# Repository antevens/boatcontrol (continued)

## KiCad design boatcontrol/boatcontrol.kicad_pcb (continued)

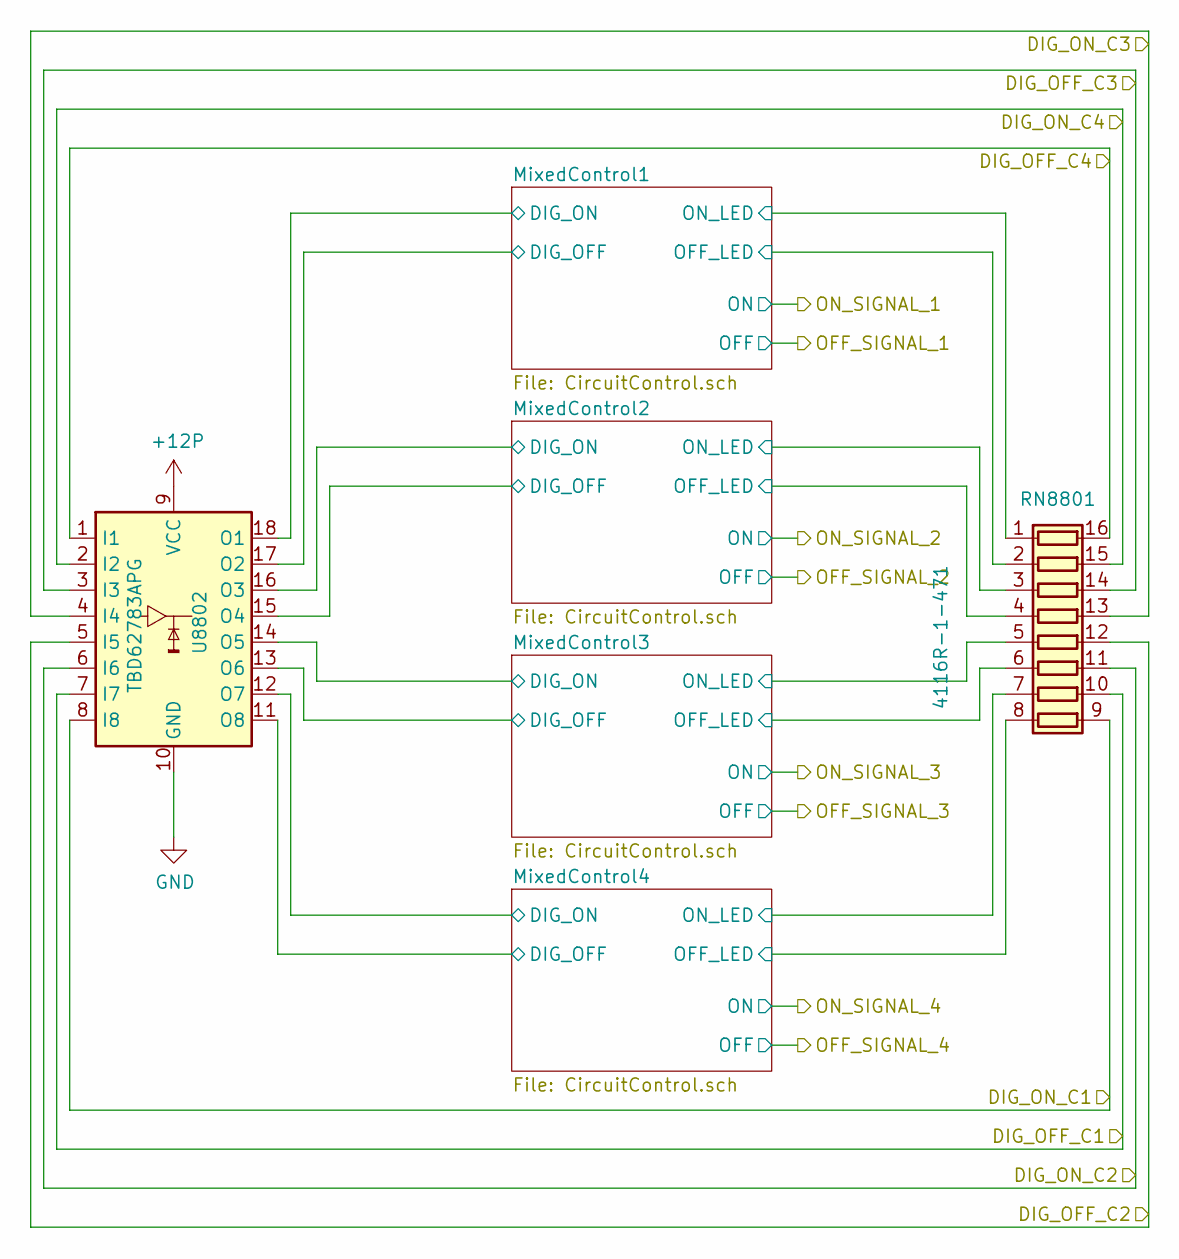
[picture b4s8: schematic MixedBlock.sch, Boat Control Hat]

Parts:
RN4001: 4116R-1-471; DIP254P762X432-16P
U4001: TBD62783APG; DIP-18_W7.62mm

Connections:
+12P: U4001.9 (VCC); also elsewhere on the board
/Add-On Relay Board 1/ADDON_C1_OFF: RN4001.10 (R7.2), U4001.7 (I7); also elsewhere on the board
/Add-On Relay Board 1/ADDON_C1_ON: RN4001.9 (R8.2), U4001.8 (I8); also elsewhere on the board
/Add-On Relay Board 1/ADDON_C2_OFF: RN4001.12 (R5.2), U4001.5 (I5); also elsewhere on the board
/Add-On Relay Board 1/ADDON_C2_ON: RN4001.11 (R6.2), U4001.6 (I6); also elsewhere on the board
/Add-On Relay Board 1/ADDON_C3_OFF: RN4001.14 (R3.2), U4001.3 (I3); also elsewhere on the board
/Add-On Relay Board 1/ADDON_C3_ON: RN4001.13 (R4.2), U4001.4 (I4); also elsewhere on the board
/Add-On Relay Board 1/ADDON_C4_OFF: RN4001.16 (R1.2), U4001.1 (I1); also elsewhere on the board
/Add-On Relay Board 1/ADDON_C4_ON: RN4001.15 (R2.2), U4001.2 (I2); also elsewhere on the board
/Add-On Relay Board 1/MixedBlock1/MixedControl1/DIG_OFF: U4001.17 (O2); also elsewhere on the board
/Add-On Relay Board 1/MixedBlock1/MixedControl1/DIG_ON: U4001.18 (O1); also elsewhere on the board
/Add-On Relay Board 1/MixedBlock1/MixedControl1/OFF_LED: RN4001.2 (R2.1); also elsewhere on the board
/Add-On Relay Board 1/MixedBlock1/MixedControl1/ON_LED: RN4001.1 (R1.1); also elsewhere on the board
/Add-On Relay Board 1/MixedBlock1/MixedControl2/DIG_OFF: U4001.15 (O4); also elsewhere on the board
/Add-On Relay Board 1/MixedBlock1/MixedControl2/DIG_ON: U4001.16 (O3); also elsewhere on the board
/Add-On Relay Board 1/MixedBlock1/MixedControl2/OFF_LED: RN4001.4 (R4.1); also elsewhere on the board
/Add-On Relay Board 1/MixedBlock1/MixedControl2/ON_LED: RN4001.3 (R3.1); also elsewhere on the board
/Add-On Relay Board 1/MixedBlock1/MixedControl3/DIG_OFF: U4001.13 (O6); also elsewhere on the board
/Add-On Relay Board 1/MixedBlock1/MixedControl3/DIG_ON: U4001.14 (O5); also elsewhere on the board
/Add-On Relay Board 1/MixedBlock1/MixedControl3/OFF_LED: RN4001.6 (R6.1); also elsewhere on the board
/Add-On Relay Board 1/MixedBlock1/MixedControl3/ON_LED: RN4001.5 (R5.1); also elsewhere on the board
/Add-On Relay Board 1/MixedBlock1/MixedControl4/DIG_OFF: U4001.11 (O8); also elsewhere on the board
/Add-On Relay Board 1/MixedBlock1/MixedControl4/DIG_ON: U4001.12 (O7); also elsewhere on the board
/Add-On Relay Board 1/MixedBlock1/MixedControl4/OFF_LED: RN4001.8 (R8.1); also elsewhere on the board
/Add-On Relay Board 1/MixedBlock1/MixedControl4/ON_LED: RN4001.7 (R7.1); also elsewhere on the board
GND: U4001.10 (GND); also elsewhere on the board

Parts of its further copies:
RN4501, RN8801, RN9301: 4116R-1-471; DIP254P762X432-16P
U4501, U8802, U9301: TBD62783APG; DIP-18_W7.62mm

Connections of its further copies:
+12P: U4501.9 (VCC), U8802.9 (VCC), U9301.9 (VCC); also elsewhere on the board
/Add-On Relay Board 1/ADDON_C5_OFF: RN4501.10 (R7.2), U4501.7 (I7); also elsewhere on the board
/Add-On Relay Board 1/ADDON_C5_ON: RN4501.9 (R8.2), U4501.8 (I8); also elsewhere on the board
/Add-On Relay Board 1/ADDON_C6_OFF: RN4501.12 (R5.2), U4501.5 (I5); also elsewhere on the board
/Add-On Relay Board 1/ADDON_C6_ON: RN4501.11 (R6.2), U4501.6 (I6); also elsewhere on the board
/Add-On Relay Board 1/ADDON_C7_OFF: RN4501.14 (R3.2), U4501.3 (I3); also elsewhere on the board
/Add-On Relay Board 1/ADDON_C7_ON: RN4501.13 (R4.2), U4501.4 (I4); also elsewhere on the board
/Add-On Relay Board 1/ADDON_C8_OFF: RN4501.16 (R1.2), U4501.1 (I1); also elsewhere on the board
/Add-On Relay Board 1/ADDON_C8_ON: RN4501.15 (R2.2), U4501.2 (I2); also elsewhere on the board
/Add-On Relay Board 1/MixedBlock2/MixedControl1/DIG_OFF: U4501.17 (O2); also elsewhere on the board
/Add-On Relay Board 1/MixedBlock2/MixedControl1/DIG_ON: U4501.18 (O1); also elsewhere on the board
/Add-On Relay Board 1/MixedBlock2/MixedControl1/OFF_LED: RN4501.2 (R2.1); also elsewhere on the board
/Add-On Relay Board 1/MixedBlock2/MixedControl1/ON_LED: RN4501.1 (R1.1); also elsewhere on the board
/Add-On Relay Board 1/MixedBlock2/MixedControl2/DIG_OFF: U4501.15 (O4); also elsewhere on the board
/Add-On Relay Board 1/MixedBlock2/MixedControl2/DIG_ON: U4501.16 (O3); also elsewhere on the board
/Add-On Relay Board 1/MixedBlock2/MixedControl2/OFF_LED: RN4501.4 (R4.1); also elsewhere on the board
/Add-On Relay Board 1/MixedBlock2/MixedControl2/ON_LED: RN4501.3 (R3.1); also elsewhere on the board
/Add-On Relay Board 1/MixedBlock2/MixedControl3/DIG_OFF: U4501.13 (O6); also elsewhere on the board
/Add-On Relay Board 1/MixedBlock2/MixedControl3/DIG_ON: U4501.14 (O5); also elsewhere on the board
/Add-On Relay Board 1/MixedBlock2/MixedControl3/OFF_LED: RN4501.6 (R6.1); also elsewhere on the board
/Add-On Relay Board 1/MixedBlock2/MixedControl3/ON_LED: RN4501.5 (R5.1); also elsewhere on the board
/Add-On Relay Board 1/MixedBlock2/MixedControl4/DIG_OFF: U4501.11 (O8); also elsewhere on the board
/Add-On Relay Board 1/MixedBlock2/MixedControl4/DIG_ON: U4501.12 (O7); also elsewhere on the board
/Add-On Relay Board 1/MixedBlock2/MixedControl4/OFF_LED: RN4501.8 (R8.1); also elsewhere on the board
/Add-On Relay Board 1/MixedBlock2/MixedControl4/ON_LED: RN4501.7 (R7.1); also elsewhere on the board
/Add-On Relay Board 2/ADDON_C1_OFF: RN8801.10 (R7.2), U8802.7 (I7); also elsewhere on the board
/Add-On Relay Board 2/ADDON_C1_ON: RN8801.9 (R8.2), U8802.8 (I8); also elsewhere on the board
/Add-On Relay Board 2/ADDON_C2_OFF: RN8801.12 (R5.2), U8802.5 (I5); also elsewhere on the board
/Add-On Relay Board 2/ADDON_C2_ON: RN8801.11 (R6.2), U8802.6 (I6); also elsewhere on the board
/Add-On Relay Board 2/ADDON_C3_OFF: RN8801.14 (R3.2), U8802.3 (I3); also elsewhere on the board
/Add-On Relay Board 2/ADDON_C3_ON: RN8801.13 (R4.2), U8802.4 (I4); also elsewhere on the board
/Add-On Relay Board 2/ADDON_C4_OFF: RN8801.16 (R1.2), U8802.1 (I1); also elsewhere on the board
/Add-On Relay Board 2/ADDON_C4_ON: RN8801.15 (R2.2), U8802.2 (I2); also elsewhere on the board
/Add-On Relay Board 2/ADDON_C5_OFF: RN9301.10 (R7.2), U9301.7 (I7); also elsewhere on the board
/Add-On Relay Board 2/ADDON_C5_ON: RN9301.9 (R8.2), U9301.8 (I8); also elsewhere on the board
/Add-On Relay Board 2/ADDON_C6_OFF: RN9301.12 (R5.2), U9301.5 (I5); also elsewhere on the board
/Add-On Relay Board 2/ADDON_C6_ON: RN9301.11 (R6.2), U9301.6 (I6); also elsewhere on the board
/Add-On Relay Board 2/ADDON_C7_OFF: RN9301.14 (R3.2), U9301.3 (I3); also elsewhere on the board
/Add-On Relay Board 2/ADDON_C7_ON: RN9301.13 (R4.2), U9301.4 (I4); also elsewhere on the board
/Add-On Relay Board 2/ADDON_C8_OFF: RN9301.16 (R1.2), U9301.1 (I1); also elsewhere on the board
/Add-On Relay Board 2/ADDON_C8_ON: RN9301.15 (R2.2), U9301.2 (I2); also elsewhere on the board
/Add-On Relay Board 2/MixedBlock1/MixedControl1/DIG_OFF: U8802.17 (O2); also elsewhere on the board
/Add-On Relay Board 2/MixedBlock1/MixedControl1/DIG_ON: U8802.18 (O1); also elsewhere on the board
/Add-On Relay Board 2/MixedBlock1/MixedControl1/OFF_LED: RN8801.2 (R2.1); also elsewhere on the board
/Add-On Relay Board 2/MixedBlock1/MixedControl1/ON_LED: RN8801.1 (R1.1); also elsewhere on the board
/Add-On Relay Board 2/MixedBlock1/MixedControl2/DIG_OFF: U8802.15 (O4); also elsewhere on the board
/Add-On Relay Board 2/MixedBlock1/MixedControl2/DIG_ON: U8802.16 (O3); also elsewhere on the board
/Add-On Relay Board 2/MixedBlock1/MixedControl2/OFF_LED: RN8801.4 (R4.1); also elsewhere on the board
/Add-On Relay Board 2/MixedBlock1/MixedControl2/ON_LED: RN8801.3 (R3.1); also elsewhere on the board
/Add-On Relay Board 2/MixedBlock1/MixedControl3/DIG_OFF: U8802.13 (O6); also elsewhere on the board
/Add-On Relay Board 2/MixedBlock1/MixedControl3/DIG_ON: U8802.14 (O5); also elsewhere on the board
/Add-On Relay Board 2/MixedBlock1/MixedControl3/OFF_LED: RN8801.6 (R6.1); also elsewhere on the board
/Add-On Relay Board 2/MixedBlock1/MixedControl3/ON_LED: RN8801.5 (R5.1); also elsewhere on the board
/Add-On Relay Board 2/MixedBlock1/MixedControl4/DIG_OFF: U8802.11 (O8); also elsewhere on the board
/Add-On Relay Board 2/MixedBlock1/MixedControl4/DIG_ON: U8802.12 (O7); also elsewhere on the board
/Add-On Relay Board 2/MixedBlock1/MixedControl4/OFF_LED: RN8801.8 (R8.1); also elsewhere on the board
/Add-On Relay Board 2/MixedBlock1/MixedControl4/ON_LED: RN8801.7 (R7.1); also elsewhere on the board
/Add-On Relay Board 2/MixedBlock2/MixedControl1/DIG_OFF: U9301.17 (O2); also elsewhere on the board
/Add-On Relay Board 2/MixedBlock2/MixedControl1/DIG_ON: U9301.18 (O1); also elsewhere on the board
/Add-On Relay Board 2/MixedBlock2/MixedControl1/OFF_LED: RN9301.2 (R2.1); also elsewhere on the board
/Add-On Relay Board 2/MixedBlock2/MixedControl1/ON_LED: RN9301.1 (R1.1); also elsewhere on the board
/Add-On Relay Board 2/MixedBlock2/MixedControl2/DIG_OFF: U9301.15 (O4); also elsewhere on the board
/Add-On Relay Board 2/MixedBlock2/MixedControl2/DIG_ON: U9301.16 (O3); also elsewhere on the board
/Add-On Relay Board 2/MixedBlock2/MixedControl2/OFF_LED: RN9301.4 (R4.1); also elsewhere on the board
/Add-On Relay Board 2/MixedBlock2/MixedControl2/ON_LED: RN9301.3 (R3.1); also elsewhere on the board
/Add-On Relay Board 2/MixedBlock2/MixedControl3/DIG_OFF: U9301.13 (O6); also elsewhere on the board
/Add-On Relay Board 2/MixedBlock2/MixedControl3/DIG_ON: U9301.14 (O5); also elsewhere on the board
/Add-On Relay Board 2/MixedBlock2/MixedControl3/OFF_LED: RN9301.6 (R6.1); also elsewhere on the board
/Add-On Relay Board 2/MixedBlock2/MixedControl3/ON_LED: RN9301.5 (R5.1); also elsewhere on the board
/Add-On Relay Board 2/MixedBlock2/MixedControl4/DIG_OFF: U9301.11 (O8); also elsewhere on the board
/Add-On Relay Board 2/MixedBlock2/MixedControl4/DIG_ON: U9301.12 (O7); also elsewhere on the board
/Add-On Relay Board 2/MixedBlock2/MixedControl4/OFF_LED: RN9301.8 (R8.1); also elsewhere on the board
/Add-On Relay Board 2/MixedBlock2/MixedControl4/ON_LED: RN9301.7 (R7.1); also elsewhere on the board
GND: U4501.10 (GND), U8802.10 (GND), U9301.10 (GND); also elsewhere on the board

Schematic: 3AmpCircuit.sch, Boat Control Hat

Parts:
CB1101: T9-818 3; Schurter_Circuit_Breaker
D1101: 20mA R/G CA; LED_D5.0mm-3
K1101: G5RL-K1A-E-DC12; RELAY_G5RL-K1A-E-DC12
SW1101, SW1102: ESB30; SW_PUSH_ESB30_DPDT

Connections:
+12C: K1101.3 (NC), K1101.6 (NC); also elsewhere on the board
+12P: D1101.2 (K), K1101.9 (C9); also elsewhere on the board
/12V DC Common Bank/12V DC Block 1/3AC1/DISABLED_INDICATOR: SW1101.3 (C), SW1102.3 (C)
/12V DC Common Bank/12V DC Block 1/3AC1/OFF: SW1101.4 (A); also elsewhere on the board
/12V DC Common Bank/12V DC Block 1/3AC1/OFF_COIL: K1101.8 (C8), SW1102.2 (B); also elsewhere on the board
/12V DC Common Bank/12V DC Block 1/3AC1/OFF_LED: D1101.3 (A2); also elsewhere on the board
/12V DC Common Bank/12V DC Block 1/3AC1/OFF_TO_ON: SW1101.5 (B), SW1102.1 (A)
/12V DC Common Bank/12V DC Block 1/3AC1/ON: SW1102.4 (A); also elsewhere on the board
/12V DC Common Bank/12V DC Block 1/3AC1/ON_COIL: K1101.1 (C1), SW1101.2 (B); also elsewhere on the board
/12V DC Common Bank/12V DC Block 1/3AC1/ON_LED: D1101.1 (A1); also elsewhere on the board
/12V DC Common Bank/12V DC Block 1/3AC1/ON_TO_OFF: SW1101.1 (A), SW1102.5 (B)
/12V DC Common Bank/12V DC Block 1/3AC1/TO_FUSE: CB1101.P1, K1101.4 (NO), K1101.5 (NO)
/12V DC Common Bank/12V DC Block 1/OUT_C1: CB1101.P2; also elsewhere on the board
GND: SW1101.6 (C), SW1102.6 (C); also elsewhere on the board

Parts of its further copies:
CB801, CB901, CB1001, CB1701, CB1801, CB1901, CB2001, CB2601, CB2701, CB2801, CB2901, CB3501, CB3601, CB3701, CB3801: T9-818 3; Schurter_Circuit_Breaker
D801, D901, D1001, D1701, D1801, D1901, D2001, D2601, D2701, D2801, D2901, D3501, D3601, D3701, D3801: 20mA R/G CA; LED_D5.0mm-3
K801, K901, K1001, K1701, K1801, K1901, K2001, K2601, K2701, K2801, K2901, K3501, K3601, K3701, K3801: G5RL-K1A-E-DC12; RELAY_G5RL-K1A-E-DC12
SW801, SW802, SW901, SW902, SW1001, SW1002, SW1701, SW1702, SW1801, SW1802, SW1901, SW1902, SW2001, SW2002, SW2601, SW2602, SW2701, SW2702, SW2801, SW2802, SW2901, SW2902, SW3501, SW3502, SW3601, SW3602, SW3701, SW3702, SW3801, SW3802: ESB30; SW_PUSH_ESB30_DPDT

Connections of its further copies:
+12C: K801.3 (NC), K801.6 (NC), K901.3 (NC), K901.6 (NC), K1001.3 (NC), K1001.6 (NC), K1701.3 (NC), K1701.6 (NC), K1801.3 (NC), K1801.6 (NC), K1901.3 (NC), K1901.6 (NC), K2001.3 (NC), K2001.6 (NC), K2601.3 (NC), K2601.6 (NC), K2701.3 (NC), K2701.6 (NC), K2801.3 (NC), K2801.6 (NC), K2901.3 (NC), K2901.6 (NC), K3501.3 (NC), K3501.6 (NC), K3601.3 (NC), K3601.6 (NC), K3701.3 (NC), K3701.6 (NC), K3801.3 (NC), K3801.6 (NC); also elsewhere on the board
+12P: D801.2 (K), D901.2 (K), D1001.2 (K), D1701.2 (K), D1801.2 (K), D1901.2 (K), D2001.2 (K), D2601.2 (K), D2701.2 (K), D2801.2 (K), D2901.2 (K), D3501.2 (K), D3601.2 (K), D3701.2 (K), D3801.2 (K), K801.9 (C9), K901.9 (C9), K1001.9 (C9), K1701.9 (C9), K1801.9 (C9), K1901.9 (C9), K2001.9 (C9), K2601.9 (C9), K2701.9 (C9), K2801.9 (C9), K2901.9 (C9), K3501.9 (C9), K3601.9 (C9), K3701.9 (C9), K3801.9 (C9); also elsewhere on the board
/12V DC Common Bank/12V DC Block 1/3AC2/DISABLED_INDICATOR: SW1001.3 (C), SW1002.3 (C)
/12V DC Common Bank/12V DC Block 1/3AC2/OFF: SW1001.4 (A); also elsewhere on the board
/12V DC Common Bank/12V DC Block 1/3AC2/OFF_COIL: K1001.8 (C8), SW1002.2 (B); also elsewhere on the board
/12V DC Common Bank/12V DC Block 1/3AC2/OFF_LED: D1001.3 (A2); also elsewhere on the board
/12V DC Common Bank/12V DC Block 1/3AC2/OFF_TO_ON: SW1001.5 (B), SW1002.1 (A)
/12V DC Common Bank/12V DC Block 1/3AC2/ON: SW1002.4 (A); also elsewhere on the board
/12V DC Common Bank/12V DC Block 1/3AC2/ON_COIL: K1001.1 (C1), SW1001.2 (B); also elsewhere on the board
/12V DC Common Bank/12V DC Block 1/3AC2/ON_LED: D1001.1 (A1); also elsewhere on the board
/12V DC Common Bank/12V DC Block 1/3AC2/ON_TO_OFF: SW1001.1 (A), SW1002.5 (B)
/12V DC Common Bank/12V DC Block 1/3AC2/TO_FUSE: CB1001.P1, K1001.4 (NO), K1001.5 (NO)
/12V DC Common Bank/12V DC Block 1/3AC3/DISABLED_INDICATOR: SW901.3 (C), SW902.3 (C)
/12V DC Common Bank/12V DC Block 1/3AC3/OFF: SW901.4 (A); also elsewhere on the board
/12V DC Common Bank/12V DC Block 1/3AC3/OFF_COIL: K901.8 (C8), SW902.2 (B); also elsewhere on the board
/12V DC Common Bank/12V DC Block 1/3AC3/OFF_LED: D901.3 (A2); also elsewhere on the board
/12V DC Common Bank/12V DC Block 1/3AC3/OFF_TO_ON: SW901.5 (B), SW902.1 (A)
/12V DC Common Bank/12V DC Block 1/3AC3/ON: SW902.4 (A); also elsewhere on the board
/12V DC Common Bank/12V DC Block 1/3AC3/ON_COIL: K901.1 (C1), SW901.2 (B); also elsewhere on the board
/12V DC Common Bank/12V DC Block 1/3AC3/ON_LED: D901.1 (A1); also elsewhere on the board
/12V DC Common Bank/12V DC Block 1/3AC3/ON_TO_OFF: SW901.1 (A), SW902.5 (B)
/12V DC Common Bank/12V DC Block 1/3AC3/TO_FUSE: CB901.P1, K901.4 (NO), K901.5 (NO)
/12V DC Common Bank/12V DC Block 1/3AC4/DISABLED_INDICATOR: SW801.3 (C), SW802.3 (C)
/12V DC Common Bank/12V DC Block 1/3AC4/OFF: SW801.4 (A); also elsewhere on the board
/12V DC Common Bank/12V DC Block 1/3AC4/OFF_COIL: K801.8 (C8), SW802.2 (B); also elsewhere on the board
/12V DC Common Bank/12V DC Block 1/3AC4/OFF_LED: D801.3 (A2); also elsewhere on the board
/12V DC Common Bank/12V DC Block 1/3AC4/OFF_TO_ON: SW801.5 (B), SW802.1 (A)
/12V DC Common Bank/12V DC Block 1/3AC4/ON: SW802.4 (A); also elsewhere on the board
/12V DC Common Bank/12V DC Block 1/3AC4/ON_COIL: K801.1 (C1), SW801.2 (B); also elsewhere on the board
/12V DC Common Bank/12V DC Block 1/3AC4/ON_LED: D801.1 (A1); also elsewhere on the board
/12V DC Common Bank/12V DC Block 1/3AC4/ON_TO_OFF: SW801.1 (A), SW802.5 (B)
/12V DC Common Bank/12V DC Block 1/3AC4/TO_FUSE: CB801.P1, K801.4 (NO), K801.5 (NO)
/12V DC Common Bank/12V DC Block 1/OUT_C2: CB1001.P2; also elsewhere on the board
/12V DC Common Bank/12V DC Block 1/OUT_C3: CB901.P2; also elsewhere on the board
/12V DC Common Bank/12V DC Block 1/OUT_C4: CB801.P2; also elsewhere on the board
/12V DC Common Bank/12V DC Block 2/3AC1/DISABLED_INDICATOR: SW2001.3 (C), SW2002.3 (C)
/12V DC Common Bank/12V DC Block 2/3AC1/OFF: SW2001.4 (A); also elsewhere on the board
/12V DC Common Bank/12V DC Block 2/3AC1/OFF_COIL: K2001.8 (C8), SW2002.2 (B); also elsewhere on the board
/12V DC Common Bank/12V DC Block 2/3AC1/OFF_LED: D2001.3 (A2); also elsewhere on the board
/12V DC Common Bank/12V DC Block 2/3AC1/OFF_TO_ON: SW2001.5 (B), SW2002.1 (A)
/12V DC Common Bank/12V DC Block 2/3AC1/ON: SW2002.4 (A); also elsewhere on the board
/12V DC Common Bank/12V DC Block 2/3AC1/ON_COIL: K2001.1 (C1), SW2001.2 (B); also elsewhere on the board
/12V DC Common Bank/12V DC Block 2/3AC1/ON_LED: D2001.1 (A1); also elsewhere on the board
/12V DC Common Bank/12V DC Block 2/3AC1/ON_TO_OFF: SW2001.1 (A), SW2002.5 (B)
/12V DC Common Bank/12V DC Block 2/3AC1/TO_FUSE: CB2001.P1, K2001.4 (NO), K2001.5 (NO)
/12V DC Common Bank/12V DC Block 2/3AC2/DISABLED_INDICATOR: SW1901.3 (C), SW1902.3 (C)
/12V DC Common Bank/12V DC Block 2/3AC2/OFF: SW1901.4 (A); also elsewhere on the board
/12V DC Common Bank/12V DC Block 2/3AC2/OFF_COIL: K1901.8 (C8), SW1902.2 (B); also elsewhere on the board
/12V DC Common Bank/12V DC Block 2/3AC2/OFF_LED: D1901.3 (A2); also elsewhere on the board
/12V DC Common Bank/12V DC Block 2/3AC2/OFF_TO_ON: SW1901.5 (B), SW1902.1 (A)
/12V DC Common Bank/12V DC Block 2/3AC2/ON: SW1902.4 (A); also elsewhere on the board
/12V DC Common Bank/12V DC Block 2/3AC2/ON_COIL: K1901.1 (C1), SW1901.2 (B); also elsewhere on the board
/12V DC Common Bank/12V DC Block 2/3AC2/ON_LED: D1901.1 (A1); also elsewhere on the board
/12V DC Common Bank/12V DC Block 2/3AC2/ON_TO_OFF: SW1901.1 (A), SW1902.5 (B)
/12V DC Common Bank/12V DC Block 2/3AC2/TO_FUSE: CB1901.P1, K1901.4 (NO), K1901.5 (NO)
/12V DC Common Bank/12V DC Block 2/3AC3/DISABLED_INDICATOR: SW1801.3 (C), SW1802.3 (C)
/12V DC Common Bank/12V DC Block 2/3AC3/OFF: SW1801.4 (A); also elsewhere on the board
/12V DC Common Bank/12V DC Block 2/3AC3/OFF_COIL: K1801.8 (C8), SW1802.2 (B); also elsewhere on the board
/12V DC Common Bank/12V DC Block 2/3AC3/OFF_LED: D1801.3 (A2); also elsewhere on the board
/12V DC Common Bank/12V DC Block 2/3AC3/OFF_TO_ON: SW1801.5 (B), SW1802.1 (A)
/12V DC Common Bank/12V DC Block 2/3AC3/ON: SW1802.4 (A); also elsewhere on the board
/12V DC Common Bank/12V DC Block 2/3AC3/ON_COIL: K1801.1 (C1), SW1801.2 (B); also elsewhere on the board
/12V DC Common Bank/12V DC Block 2/3AC3/ON_LED: D1801.1 (A1); also elsewhere on the board
/12V DC Common Bank/12V DC Block 2/3AC3/ON_TO_OFF: SW1801.1 (A), SW1802.5 (B)
/12V DC Common Bank/12V DC Block 2/3AC3/TO_FUSE: CB1801.P1, K1801.4 (NO), K1801.5 (NO)
/12V DC Common Bank/12V DC Block 2/3AC4/DISABLED_INDICATOR: SW1701.3 (C), SW1702.3 (C)
/12V DC Common Bank/12V DC Block 2/3AC4/OFF: SW1701.4 (A); also elsewhere on the board
/12V DC Common Bank/12V DC Block 2/3AC4/OFF_COIL: K1701.8 (C8), SW1702.2 (B); also elsewhere on the board
/12V DC Common Bank/12V DC Block 2/3AC4/OFF_LED: D1701.3 (A2); also elsewhere on the board
/12V DC Common Bank/12V DC Block 2/3AC4/OFF_TO_ON: SW1701.5 (B), SW1702.1 (A)
/12V DC Common Bank/12V DC Block 2/3AC4/ON: SW1702.4 (A); also elsewhere on the board
/12V DC Common Bank/12V DC Block 2/3AC4/ON_COIL: K1701.1 (C1), SW1701.2 (B); also elsewhere on the board
/12V DC Common Bank/12V DC Block 2/3AC4/ON_LED: D1701.1 (A1); also elsewhere on the board
/12V DC Common Bank/12V DC Block 2/3AC4/ON_TO_OFF: SW1701.1 (A), SW1702.5 (B)
/12V DC Common Bank/12V DC Block 2/3AC4/TO_FUSE: CB1701.P1, K1701.4 (NO), K1701.5 (NO)
/12V DC Common Bank/12V DC Block 2/OUT_C1: CB2001.P2; also elsewhere on the board
/12V DC Common Bank/12V DC Block 2/OUT_C2: CB1901.P2; also elsewhere on the board
/12V DC Common Bank/12V DC Block 2/OUT_C3: CB1801.P2; also elsewhere on the board
/12V DC Common Bank/12V DC Block 2/OUT_C4: CB1701.P2; also elsewhere on the board
/12V DC Common Bank/12V DC Block 3/3AC1/DISABLED_INDICATOR: SW2901.3 (C), SW2902.3 (C)
/12V DC Common Bank/12V DC Block 3/3AC1/OFF: SW2901.4 (A); also elsewhere on the board
/12V DC Common Bank/12V DC Block 3/3AC1/OFF_COIL: K2901.8 (C8), SW2902.2 (B); also elsewhere on the board
/12V DC Common Bank/12V DC Block 3/3AC1/OFF_LED: D2901.3 (A2); also elsewhere on the board
/12V DC Common Bank/12V DC Block 3/3AC1/OFF_TO_ON: SW2901.5 (B), SW2902.1 (A)
/12V DC Common Bank/12V DC Block 3/3AC1/ON: SW2902.4 (A); also elsewhere on the board
/12V DC Common Bank/12V DC Block 3/3AC1/ON_COIL: K2901.1 (C1), SW2901.2 (B); also elsewhere on the board
/12V DC Common Bank/12V DC Block 3/3AC1/ON_LED: D2901.1 (A1); also elsewhere on the board
/12V DC Common Bank/12V DC Block 3/3AC1/ON_TO_OFF: SW2901.1 (A), SW2902.5 (B)
/12V DC Common Bank/12V DC Block 3/3AC1/TO_FUSE: CB2901.P1, K2901.4 (NO), K2901.5 (NO)
/12V DC Common Bank/12V DC Block 3/3AC2/DISABLED_INDICATOR: SW2801.3 (C), SW2802.3 (C)
/12V DC Common Bank/12V DC Block 3/3AC2/OFF: SW2801.4 (A); also elsewhere on the board
/12V DC Common Bank/12V DC Block 3/3AC2/OFF_COIL: K2801.8 (C8), SW2802.2 (B); also elsewhere on the board
/12V DC Common Bank/12V DC Block 3/3AC2/OFF_LED: D2801.3 (A2); also elsewhere on the board
/12V DC Common Bank/12V DC Block 3/3AC2/OFF_TO_ON: SW2801.5 (B), SW2802.1 (A)
/12V DC Common Bank/12V DC Block 3/3AC2/ON: SW2802.4 (A); also elsewhere on the board
/12V DC Common Bank/12V DC Block 3/3AC2/ON_COIL: K2801.1 (C1), SW2801.2 (B); also elsewhere on the board
/12V DC Common Bank/12V DC Block 3/3AC2/ON_LED: D2801.1 (A1); also elsewhere on the board
/12V DC Common Bank/12V DC Block 3/3AC2/ON_TO_OFF: SW2801.1 (A), SW2802.5 (B)
/12V DC Common Bank/12V DC Block 3/3AC2/TO_FUSE: CB2801.P1, K2801.4 (NO), K2801.5 (NO)
/12V DC Common Bank/12V DC Block 3/3AC3/DISABLED_INDICATOR: SW2701.3 (C), SW2702.3 (C)
/12V DC Common Bank/12V DC Block 3/3AC3/OFF: SW2701.4 (A); also elsewhere on the board
/12V DC Common Bank/12V DC Block 3/3AC3/OFF_COIL: K2701.8 (C8), SW2702.2 (B); also elsewhere on the board
/12V DC Common Bank/12V DC Block 3/3AC3/OFF_LED: D2701.3 (A2); also elsewhere on the board
/12V DC Common Bank/12V DC Block 3/3AC3/OFF_TO_ON: SW2701.5 (B), SW2702.1 (A)
/12V DC Common Bank/12V DC Block 3/3AC3/ON: SW2702.4 (A); also elsewhere on the board
/12V DC Common Bank/12V DC Block 3/3AC3/ON_COIL: K2701.1 (C1), SW2701.2 (B); also elsewhere on the board
/12V DC Common Bank/12V DC Block 3/3AC3/ON_LED: D2701.1 (A1); also elsewhere on the board
/12V DC Common Bank/12V DC Block 3/3AC3/ON_TO_OFF: SW2701.1 (A), SW2702.5 (B)
/12V DC Common Bank/12V DC Block 3/3AC3/TO_FUSE: CB2701.P1, K2701.4 (NO), K2701.5 (NO)
/12V DC Common Bank/12V DC Block 3/3AC4/DISABLED_INDICATOR: SW2601.3 (C), SW2602.3 (C)
/12V DC Common Bank/12V DC Block 3/3AC4/OFF: SW2601.4 (A); also elsewhere on the board
/12V DC Common Bank/12V DC Block 3/3AC4/OFF_COIL: K2601.8 (C8), SW2602.2 (B); also elsewhere on the board
/12V DC Common Bank/12V DC Block 3/3AC4/OFF_LED: D2601.3 (A2); also elsewhere on the board
/12V DC Common Bank/12V DC Block 3/3AC4/OFF_TO_ON: SW2601.5 (B), SW2602.1 (A)
/12V DC Common Bank/12V DC Block 3/3AC4/ON: SW2602.4 (A); also elsewhere on the board
/12V DC Common Bank/12V DC Block 3/3AC4/ON_COIL: K2601.1 (C1), SW2601.2 (B); also elsewhere on the board
/12V DC Common Bank/12V DC Block 3/3AC4/ON_LED: D2601.1 (A1); also elsewhere on the board
/12V DC Common Bank/12V DC Block 3/3AC4/ON_TO_OFF: SW2601.1 (A), SW2602.5 (B)
/12V DC Common Bank/12V DC Block 3/3AC4/TO_FUSE: CB2601.P1, K2601.4 (NO), K2601.5 (NO)
/12V DC Common Bank/12V DC Block 3/OUT_C1: CB2901.P2; also elsewhere on the board
/12V DC Common Bank/12V DC Block 3/OUT_C2: CB2801.P2; also elsewhere on the board
/12V DC Common Bank/12V DC Block 3/OUT_C3: CB2701.P2; also elsewhere on the board
/12V DC Common Bank/12V DC Block 3/OUT_C4: CB2601.P2; also elsewhere on the board
/12V DC Common Bank/12V DC Block 4/3AC1/DISABLED_INDICATOR: SW3801.3 (C), SW3802.3 (C)
/12V DC Common Bank/12V DC Block 4/3AC1/OFF: SW3801.4 (A); also elsewhere on the board
/12V DC Common Bank/12V DC Block 4/3AC1/OFF_COIL: K3801.8 (C8), SW3802.2 (B); also elsewhere on the board
/12V DC Common Bank/12V DC Block 4/3AC1/OFF_LED: D3801.3 (A2); also elsewhere on the board
/12V DC Common Bank/12V DC Block 4/3AC1/OFF_TO_ON: SW3801.5 (B), SW3802.1 (A)
/12V DC Common Bank/12V DC Block 4/3AC1/ON: SW3802.4 (A); also elsewhere on the board
/12V DC Common Bank/12V DC Block 4/3AC1/ON_COIL: K3801.1 (C1), SW3801.2 (B); also elsewhere on the board
/12V DC Common Bank/12V DC Block 4/3AC1/ON_LED: D3801.1 (A1); also elsewhere on the board
/12V DC Common Bank/12V DC Block 4/3AC1/ON_TO_OFF: SW3801.1 (A), SW3802.5 (B)
/12V DC Common Bank/12V DC Block 4/3AC1/TO_FUSE: CB3801.P1, K3801.4 (NO), K3801.5 (NO)
/12V DC Common Bank/12V DC Block 4/3AC2/DISABLED_INDICATOR: SW3701.3 (C), SW3702.3 (C)
/12V DC Common Bank/12V DC Block 4/3AC2/OFF: SW3701.4 (A); also elsewhere on the board
/12V DC Common Bank/12V DC Block 4/3AC2/OFF_COIL: K3701.8 (C8), SW3702.2 (B); also elsewhere on the board
/12V DC Common Bank/12V DC Block 4/3AC2/OFF_LED: D3701.3 (A2); also elsewhere on the board
/12V DC Common Bank/12V DC Block 4/3AC2/OFF_TO_ON: SW3701.5 (B), SW3702.1 (A)
/12V DC Common Bank/12V DC Block 4/3AC2/ON: SW3702.4 (A); also elsewhere on the board
/12V DC Common Bank/12V DC Block 4/3AC2/ON_COIL: K3701.1 (C1), SW3701.2 (B); also elsewhere on the board
/12V DC Common Bank/12V DC Block 4/3AC2/ON_LED: D3701.1 (A1); also elsewhere on the board
/12V DC Common Bank/12V DC Block 4/3AC2/ON_TO_OFF: SW3701.1 (A), SW3702.5 (B)
/12V DC Common Bank/12V DC Block 4/3AC2/TO_FUSE: CB3701.P1, K3701.4 (NO), K3701.5 (NO)
/12V DC Common Bank/12V DC Block 4/3AC3/DISABLED_INDICATOR: SW3601.3 (C), SW3602.3 (C)
/12V DC Common Bank/12V DC Block 4/3AC3/OFF: SW3601.4 (A); also elsewhere on the board
/12V DC Common Bank/12V DC Block 4/3AC3/OFF_COIL: K3601.8 (C8), SW3602.2 (B); also elsewhere on the board
/12V DC Common Bank/12V DC Block 4/3AC3/OFF_LED: D3601.3 (A2); also elsewhere on the board
/12V DC Common Bank/12V DC Block 4/3AC3/OFF_TO_ON: SW3601.5 (B), SW3602.1 (A)
/12V DC Common Bank/12V DC Block 4/3AC3/ON: SW3602.4 (A); also elsewhere on the board
/12V DC Common Bank/12V DC Block 4/3AC3/ON_COIL: K3601.1 (C1), SW3601.2 (B); also elsewhere on the board
/12V DC Common Bank/12V DC Block 4/3AC3/ON_LED: D3601.1 (A1); also elsewhere on the board
/12V DC Common Bank/12V DC Block 4/3AC3/ON_TO_OFF: SW3601.1 (A), SW3602.5 (B)
/12V DC Common Bank/12V DC Block 4/3AC3/TO_FUSE: CB3601.P1, K3601.4 (NO), K3601.5 (NO)
/12V DC Common Bank/12V DC Block 4/3AC4/DISABLED_INDICATOR: SW3501.3 (C), SW3502.3 (C)
/12V DC Common Bank/12V DC Block 4/3AC4/OFF: SW3501.4 (A); also elsewhere on the board
/12V DC Common Bank/12V DC Block 4/3AC4/OFF_COIL: K3501.8 (C8), SW3502.2 (B); also elsewhere on the board
/12V DC Common Bank/12V DC Block 4/3AC4/OFF_LED: D3501.3 (A2); also elsewhere on the board
/12V DC Common Bank/12V DC Block 4/3AC4/OFF_TO_ON: SW3501.5 (B), SW3502.1 (A)
/12V DC Common Bank/12V DC Block 4/3AC4/ON: SW3502.4 (A); also elsewhere on the board
/12V DC Common Bank/12V DC Block 4/3AC4/ON_COIL: K3501.1 (C1), SW3501.2 (B); also elsewhere on the board
/12V DC Common Bank/12V DC Block 4/3AC4/ON_LED: D3501.1 (A1); also elsewhere on the board
/12V DC Common Bank/12V DC Block 4/3AC4/ON_TO_OFF: SW3501.1 (A), SW3502.5 (B)
/12V DC Common Bank/12V DC Block 4/3AC4/TO_FUSE: CB3501.P1, K3501.4 (NO), K3501.5 (NO)
/12V DC Common Bank/12V DC Block 4/OUT_C1: CB3801.P2; also elsewhere on the board
/12V DC Common Bank/12V DC Block 4/OUT_C2: CB3701.P2; also elsewhere on the board
/12V DC Common Bank/12V DC Block 4/OUT_C3: CB3601.P2; also elsewhere on the board
/12V DC Common Bank/12V DC Block 4/OUT_C4: CB3501.P2; also elsewhere on the board
GND: SW801.6 (C), SW802.6 (C), SW901.6 (C), SW902.6 (C), SW1001.6 (C), SW1002.6 (C), SW1701.6 (C), SW1702.6 (C), SW1801.6 (C), SW1802.6 (C), SW1901.6 (C), SW1902.6 (C), SW2001.6 (C), SW2002.6 (C), SW2601.6 (C), SW2602.6 (C), SW2701.6 (C), SW2702.6 (C), SW2801.6 (C), SW2802.6 (C), SW2901.6 (C), SW2902.6 (C), SW3501.6 (C), SW3502.6 (C), SW3601.6 (C), SW3602.6 (C), SW3701.6 (C), SW3702.6 (C), SW3801.6 (C), SW3802.6 (C); also elsewhere on the board

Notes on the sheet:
Buttons offer manual overide of relays using direct 12V. There is no timing/pulse circuit when operating the switches so care should be taken not to energise relay coils for more than a few seconds. Setting each coil to "on" will disable the opposing coil to prevent both coils from being energnized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
